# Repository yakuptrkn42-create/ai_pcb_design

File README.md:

# AİES — kalp anatomi eğitim cihazı

**Güncel teslim:** videodan gözlem kaydı ve ayrı bir bağlantı önerisi; paylaşılan üç blok görseli KiCad sayfaları olarak da oluşturuldu.

- [Tüm KiCad projeleri, PDF, parça/GPIO tabloları ve video kanıtları — ZIP](AIES_Kalp_Anatomi_KiCad_Rev1.zip)
- [Bağlantı önerisi P1 — 7 sayfalı PDF](AIES_Video_Schematic_Review_R1/PDF/AIES_Oneri_P1.pdf)
- [Video inceleme raporu ve yakın görüntüler — PDF](AIES_Video_Schematic_Review_R1/PDF/Inceleme_Raporu_TR.pdf)
- [Açılış ve kapsam](AIES_Video_Schematic_Review_R1/README_TR.md) · [Zaman/kesinlik tablosu](AIES_Video_Schematic_Review_R1/Review/Inceleme_Tablosu.csv)

Öneri projesini `AIES_Video_Schematic_Review_R1/Proposal/Project/AIES_Oneri_P1.kicad_pro` ile KiCad 9'da açın. **P1 ERC: 0 hata / 0 uyarı; 157 pin–net eşlemesi kontrol edildi.** GPIO/adres/LED sırası mühendislik seçimidir; mevcut yüklü firmware uyumu bilinmiyor, uyarlama gerektirir.

`Project/` altındaki video kaydı ayrı tutuldu: bilinmeyen kablolar/GPIO tahmin edilmedi; 68 açık terminal + 8 besleme-sürücü ERC bulgusu saklanmadı. Küçük video 148,89 saniye / 480×848; 3 × 8 görünür LED gövdesi sayıldı. Ses konuşması incelenemedi. Exact modül, güç/USB ve üretici limitleri açık; PCB/firmware veya fiziksel test yapılmadı. Üretime hazır onayı verilmedi.

---

# Güncel teslim — Rev J / Routing R2

**Güncel yüklenen Project.zip temel alınarak routing tamamlandı. 0 DRC ihlali / 0 açık bağlantı / 0 şematik–PCB farkı / ERC 0 hata ve 0 uyarı.**

- [Doğrudan indir — KiCad + Gerber/drill + rapor ZIP](https://github.com/yakuptrkn42-create/ai_pcb_design/raw/refs/heads/main/STM32F469_DISEN_RevJ_Routing_R2.zip)
- [Yalnız üreticiye aktarım dosyaları — CAM ZIP](https://github.com/yakuptrkn42-create/ai_pcb_design/raw/refs/heads/main/STM32F469_DISEN_RevJ_Routing_R2_Fabrication.zip)
- [Beş sayfalık teknik rapor — PDF](SingleLCD_RevJ_Routing_R2/PDF/Routing_R2_Review_TR.pdf)
- [Düzenlenebilir KiCad projesi](SingleLCD_RevJ_Routing_R2/Project/) · [Açılış ve kapsam](SingleLCD_RevJ_Routing_R2/README_TR.md)
- [Gerber/drill doğrulaması](SingleLCD_RevJ_Routing_R2/Verification/Manufacturing_Audit.json) · [Bağımsız elektriksel/routing denetimi](SingleLCD_RevJ_Routing_R2/Verification/Validation_Summary.json)

55 × 45 mm / dört katman; J1/J2/J3 ve dört montaj deliği aynı konumda. DSI iletkenleri ~32,824 mm, her birinde iki via; çift içi planar fark <0,001 mm. İki iç GND düzlemi, backlight güç/Kelvin yolları ve eksik kontrol/besleme bağlantıları tamamlandı. SW dal toplamı 5,54 mm / 0,6 mm; 5 V ana yolları 0,8 mm. R13 8,2k/%1; J6 polarite yazısı düzeltildi. Kaynak 159 pin–net üyeliği korunur.

**Üretim kabulü koşullu:** 100 Ω hedefi için 99,4 Ω maskesiz 2D tahmin nominal kesite aittir; gerçek üretici kesiti/bitmiş geometri ve empedans kabulü henüz doğrulanmadı. FPC/kasa, parça rating'leri, touch gerilim toleransı ve yük/OVP/SI testleri raporda açıktır. Gerber/drill hazırlanmış olması fiziksel çalışma garantisi değildir. CAM ZIP içindeki aktarım koşulları imalat öncesi uygulanmalıdır.

ZIP'i tamamen çıkarıp `SingleLCD_RevJ_Routing_R2/Project/STM32F469_DISEN_RevJ_Prep1.kicad_pro` dosyasını KiCad 9 ile açın. Aşağıdaki teslimler tarihsel olarak korunur; güncel R2 projesiyle karıştırılmamalıdır.

---

# Korunan PCB yerleşimi — J-SR1 / Placement P3

**Placement tamamlandı; routing yapılmadı.** Son J-SR1 şematiği korunarak 55 × 45 mm / dört katmanlı kart yeniden yerleştirildi. J1 sol, J2/J3 üst kenara alındı; DSI için açık L koridoru ve sağ altta kompakt TPS61165 bloğu oluşturuldu. Dört montaj deliği aynı konumda kaldı.

- [Doğrudan indir — P3 KiCad ZIP](https://github.com/yakuptrkn42-create/ai_pcb_design/raw/refs/heads/main/STM32F469_DISEN_RevJ_Placement_P3.zip)
- [Yerleşim incelemesi — dört sayfalık PDF](SingleLCD_RevJ_Placement_P3/PDF/Placement_P3_Review_TR.pdf)
- [Düzenlenebilir KiCad projesi](SingleLCD_RevJ_Placement_P3/Project/) · [Açılış ve kapsam](SingleLCD_RevJ_Placement_P3/README_TR.md)
- [Routing alanı ve via adayları](SingleLCD_RevJ_Placement_P3/Views/Routing_Plan.png) · [Routing devir notları](SingleLCD_RevJ_Placement_P3/Engineering/ROUTING_HANDOFF_TR.md)
- [Doğrulama özeti](SingleLCD_RevJ_Placement_P3/Verification/Validation_Summary.json) · [Taşınabilir proje kontrolü](SingleLCD_RevJ_Placement_P3/Verification/Portable_Check.json)

**0 fiziksel DRC ihlali / 0 parity farkı / ERC 0 hata ve 0 uyarı.** Kartta 0 iz, 0 via ve 0 bakır dolgu var; montaj donanımı için dört keepout/rule area var. Routing yapılmadığı için 115 bağlantısız öğe kaydı beklenir. Üç şematik dosyası byte düzeyinde değişmedi; komponent değerleri, footprint kimlikleri ve pin bağlantıları J-SR1 ile eşleşir.

100 Ω ve iz/skew/via bütçeleri tasarım hedefleridir; üretici stackup'ı ve gerçek routing ile doğrulanmalıdır. İç GND katmanları henüz boş. FPC modelleri nominal; J6 gövdesinin 3D modeli yok. Exact kablo/kasa uyumu fiziksel teyit gerektirir. Bu paket üretim çıktısı değildir; aşağıdaki eski routing teslimleri P3'e uygulanmaz.

ZIP'i tamamen çıkarıp `SingleLCD_RevJ_Placement_P3/Project/STM32F469_DISEN_RevJ_Prep1.kicad_pro` dosyasını KiCad 9 ile açın.

---

# Yeni şematik inceleme — J-SR1

- [KiCad proje paketini indir — ZIP](STM32F469_DISEN_J_SR1_Schematic_Review.zip?raw=true)
- [Revize şematik — PDF](Schematic_RevJ_SR1_Review/PDF/Schematic_J_SR1.pdf)
- [Beş sayfalık teknik rapor — PDF](Schematic_RevJ_SR1_Review/PDF/Engineering_Review_TR.pdf)
- [Native KiCad projesi ve açılış notları](Schematic_RevJ_SR1_Review/README_TR.md)

22 Ekim 2026 tarihinde yüklenen proje üzerinde elektriksel şematik incelemesi: **ERC 0 hata / 0 uyarı**. J6 polarite açıklaması ve J4 konnektör/footprint tanımı düzeltildi; R13 8,2 kΩ yapıldı. 39 LCD pini, 25 host CN10 pini ve 53 footprint'in pin üyeliği doğrulandı. Kaynak ZIP değiştirilmeden paketlendi.

**Koşullu teslim:** host 3,365 V toleransı / touch 3,3 V üst sınırı için DISEN teyidi; gerçek FPC sürekliliği ve OVP açık-yük testleri bekleniyor. Donanımda çalışma ve nihai PCB dondurma onayı verilmedi. Bu revizyon şematik içindir; aşağıdaki önceki routing teslimi güncellenmedi.

---

# DISEN LCD — Rev J / Routing R1

**Güncel teslim: dört katman routing tamamlandı. 0 DRC ihlali / 0 bağlantısız öğe / 0 şematik–PCB parity farkı.**

- [Tek ZIP — KiCad proje, 2D/3D, rapor, Gerber ve drill](STM32F469_DISEN_RevJ_Routing_R1.zip)
- [Kısa mühendislik raporu ve PCB görselleri — PDF](SingleLCD_RevJ_Routing_R1/PDF/Routing_R1_Review_TR.pdf)
- [Native KiCad projesi](SingleLCD_RevJ_Routing_R1/Project/) · [Açılış ve doğrulama notları](SingleLCD_RevJ_Routing_R1/README_TR.md)
- [Final DRC](SingleLCD_RevJ_Routing_R1/Verification/DRC_Final.txt) · [Stackup / kurallar](SingleLCD_RevJ_Routing_R1/Engineering/Stackup_And_Rules_TR.md) · [CAM doğrulaması](SingleLCD_RevJ_Routing_R1/Verification/Manufacturing_Audit.json)

55 × 45 mm, nominal 1,6 mm / dört katman. J1/J2 ana konnektörleri aynı konum/yönde; şematik netler ve değerler korundu. 5 V yolları 0,8 mm; DSI iletkenleri iki via ile ~32,824 mm, çift içi fiziksel fark <0,01 mm. 49 devre referansı / 44 net / 159 pad–net üyeliği. ERC 0 hata / 3 mevcut etiket uyarısı. Yerleşim değişiklikleri raporda ve CSV/JSON dosyalarında açıklandı.

**Üretici henüz seçilmedi:** stackup/100 Ω hedefi nominaldir; üretici empedans teyidi ve rapordaki FPC/parça/OVP koşulları kapanmalıdır. Gerber/drill son mühendislik incelemesi içindir; fiziksel çalışma garantisi verilmez. Orijinal yüklenen ZIP korundu; önceki projeler ayrı duruyor.

ZIP'i tamamen çıkarıp `SingleLCD_RevJ_Routing_R1/Project/STM32F469_DISEN_RevJ_Prep1.kicad_pro` dosyasını KiCad 9 ile açın. GitHub ZIP sayfasındaki **Download raw file** düğmesiyle indirebilirsiniz.

---

# Korunan önceki placement — Rev J P2

**Önceki LCD teslimi:** yeni yüklenen Project.zip üzerinde son şematik kontrolü ve dört katmanlı placement optimizasyonu.

- [Tek ZIP — tüm proje dosyaları](STM32F469_DISEN_RevJ_Placement_P2.zip)
- [Kısa değerlendirme ve PCB görselleri — PDF](SingleLCD_RevJ_Placement_P2/PDF/Placement_P2_Review_TR.pdf)
- [Güncel şematik — PDF](SingleLCD_RevJ_Placement_P2/PDF/STM32F469_DISEN_RevJ_Placement_P2.pdf)
- [Native KiCad projesi](SingleLCD_RevJ_Placement_P2/Project/) · [Açılış notları](SingleLCD_RevJ_Placement_P2/README_TR.md)

55 × 45 mm, nominal 1,6 mm / dört katman; 49 devre referansı ve kullanıcının dört Ø3,5 mm montaj deliği. J6'nın yanlış polarite açıklaması **1=+5V / 2=GND** olarak düzeltildi; J4 üç kablolu PWM/reset/GND arayüzü doğru adlandırıldı. Elektriksel netler değişmedi: 44 net / 159 pin–net üyeliği aynı. Dokuz kart dışı test noktası içeri alındı; üç konnektör yaklaşımı karşılaştırıldı, ortak DSI kenarı ve kısa boost döngüleri seçildi.

**0 iz / 0 via / 0 zone.** ERC 0 hata / 3 mevcut uyarı; fiziksel DRC 0; şema–PCB parity 0. Routing yapılmadığından 115 bağlantısız öğe kaydı açık. Stackup/empedans ve FPC exact mekanik teyitleri raporda açık; üretim kabulü verilmedi. Routing ayrı onay bekler.

ZIP'i tamamen çıkarın ve `SingleLCD_RevJ_Placement_P2/Project/STM32F469_DISEN_RevJ_Prep1.kicad_pro` dosyasını KiCad 9 ile açın. Kaynak basename korunmuş, başlıklar Placement P2 yapılmıştır. GitHub ZIP sayfasındaki **Download raw file** düğmesini kullanabilirsiniz.

---

## Entegre 2S batarya paketi — Rev A

İnfüzyon pompası için iki adet 18650 hücre, BMS ve sabit dört kontaklı dock bağlantısını birleştiren **tasarımcıya aktarım ön tasarımı**.

- [Tüm proje paketi — ZIP](Integrated_Battery_Pack_RevA.zip)
- [Görsel tasarım raporu — PDF](Integrated_Battery_Pack_RevA/Tasarimciya_Aktarim_TR.pdf)
- [KiCad proje dosyaları](Integrated_Battery_Pack_RevA/Project/)
- [STEP / WRL / FreeCAD montajı](Integrated_Battery_Pack_RevA/Mechanical/)
- [Kapsam ve açılış notları](Integrated_Battery_Pack_RevA/README_TR.md)

Nominal 7,4 V / 3500 mAh; yaklaşık 2 A hedefi; 74 × 42 × 29,12 mm nominal montaj zarfı. Kaynak şematik boş olduğundan bağlantılar PCB'den geri kazanıldı. ERC, fiziksel DRC, açık bağlantı ve şema–PCB eşleşme kontrolleri temizdir; IC işlevleri ve BMS ayarları henüz doğrulanmamıştır. **Üretim veya klinik kullanım onayı yoktur.** Kesin hücre, NTC/host uyumu ve fiziksel numune testleri tasarımcı tarafından tamamlanmalıdır.

---

# STM32F469I-DISCO / DISEN — Rev J komponent yerleşimi

**Korunan önceki teslim: DS070HSD39T-132 için Placement P1.** Onaylı tek LCD şematiği korunarak 49 devre footprint’i yerleştirildi. Çift LCD Rev K ayrı korunuyor.

- [Yerleşim teslimatı — ZIP](STM32F469_DISEN_RevJ_Placement_P1.zip)
- [Yerleşim incelemesi — PDF](SingleLCD_RevJ_Placement_P1/PDF/Placement_Review_TR.pdf)
- [Native KiCad projesi](SingleLCD_RevJ_Placement_P1/Project/)
- [Açılış ve kapsam](SingleLCD_RevJ_Placement_P1/README_TR.md)

50 × 42 mm, R2 köşe, nominal 1,6 mm / 4 katman, üst yüz montajı; dört Ø2,7 mm bağlantısız M2.5 montaj deliği. Üç yerleşim yaklaşımı karşılaştırıldı, routing/SI düzeni seçildi ve yeniden iyileştirildi. Şematik, değerler, 57 net / 172 pin–net üyeliği ve mevcut kurallar korundu.

**0 iz / 0 via / 0 zone.** Yerleşim DRC’si 0 fiziksel ihlal, şema–PCB parity 0 fark; routing yapılmadığından 115 bağlantısız öğe kaydı açıktır. ERC 0 hata / 3 mevcut uyarı. Routing, yerleşim onayını bekler. FPC modelleri nominal; exact kontak/latch/kablo ve üretici stackup/empedans teyitleri raporda açıktır.

ZIP’i tamamen çıkarıp `SingleLCD_RevJ_Placement_P1/Project/STM32F469_DISEN_RevJ_Prep1.kicad_pro` dosyasını KiCad 9 ile açın. Onaylı şematiği byte düzeyinde korumak için kaynak basename korunmuştur. GitHub ZIP sayfasında **Download raw file** kullanılabilir.

## Korunan tek LCD PCB hazırlığı

**Güncel çalışma: DS070HSD39T-132 için Rev J / PCB Hazırlık 1.** Yüklenen eski Rev J esas alındı; çift LCD Rev K ayrı korunuyor.

- [Tek LCD hazırlık teslimatı — ZIP](STM32F469_DISEN_RevJ_PCBPrep1.zip)
- [KiCad proje ve kütüphaneleri](SingleLCD_RevJ_PCBPrep/Project/)
- [Doğrulama raporu — PDF](SingleLCD_RevJ_PCBPrep/PDF/Validation_RevJ_Prep1_TR.pdf)
- [Şematik — PDF](SingleLCD_RevJ_PCBPrep/PDF/STM32F469_DISEN_RevJ_Prep1.pdf)
- [Açılış ve kapsam](SingleLCD_RevJ_PCBPrep/README_TR.md)

49 footprint, 57 net ve 49 model bağı; 172 pin/net kontrolü; şema–PCB parity **0 fark**, ERC **0 hata / 3 açıklanmış uyarı**. Elektriksel bağlantılar ve değerler Rev J ile aynıdır. 4 katmanlı nominal stackup ve routing kuralları kaydedildi.

**Yerleşim henüz yapılmadı:** komponentler başlangıç aktarımı olarak (0,0)'da üst üste durur. Kart sınırı, iz, via ve dolgu yoktur. Bu aşamanın DRC çakışmaları gizlenmeden paketlendi; üretim kabulü verilmedi. FPC ve endüktör modelleri nominaldir; exact mekanik/panel/OVP ve üretici stackup koşulları raporda açıktır. Model kontrol panosu görüntüleri adaptör yerleşimi değildir.

ZIP'i tamamen çıkarıp `SingleLCD_RevJ_PCBPrep/Project/STM32F469_DISEN_RevJ_Prep1.kicad_pro` dosyasını KiCad 9 ile açın. GitHub ZIP sayfasındaki **Download raw file** düğmesiyle indirebilirsiniz.

# Korunan çift LCD çalışması — Rev K

**Güncel teslim: ortak 39 pinli donanım ve seçilebilir backlight OVP şematiği.** LCD-A: DS070HSD39T-132; LCD-B: DS0700BOE1A39CO-0180A.

- [Tüm Rev K dosyaları — ZIP](STM32F469_DISEN_RevK_DualLCD_Review.zip)
- [Gerçek şematik, 4 sayfa — PDF](Schematic_RevK_DualLCD/PDF/STM32F469_DISEN_RevK_DualLCD.pdf)
- [Türkçe mühendislik incelemesi — PDF](Schematic_RevK_DualLCD/PDF/Dual_LCD_Engineering_Review_TR.pdf)
- [Açılış, karşılaştırma ve montaj tablosu](Schematic_RevK_DualLCD/README_TR.md)
- [Native KiCad projesi](Schematic_RevK_DualLCD/Project/) · [BOM](Schematic_RevK_DualLCD/BOM/BOM_RevK_FACTORY_HOLD.csv) · [ERC](Schematic_RevK_DualLCD/Verification/ERC_RevK.txt)

**Yeni LCD için yalnızca mekanik çizim mevcut; tam elektriksel uyumluluk onayı verilmedi.** VCI/VDD gerilim aralıkları ve maksimum LED değerleri eksiktir. Varsayılan R4/R23 DNP montajı bir onay bekletme durumudur; tam izolasyon değildir. Panel-B, eksik veriler kapanmadan bağlanıp enerjilendirilmemelidir.

R7 her iki panel için 5,23 Ω / nominal 38,24 mA kaldı. JP1 yalnızca OVP eşiğini seçer: A 2–3 HIGH ≈28,69 V; B 1–2 LOW ≈14,94 V (geçici aday). MIPI yollarına anahtar eklenmedi. ERC: **0 hata / 3 açıklanmış uyarı**; kurallar değiştirilmedi. PCB ve yazılım bu aşamada değiştirilmedi. Eski PCB'ler yeni dört footprint ve bağlantılar için ECO gerektirir.

ZIP'i tamamen çıkarıp `Schematic_RevK_DualLCD/Project/STM32F469_DISEN_RevK.kicad_pro` dosyasını KiCad 9 ile açın. GitHub ZIP sayfasındaki **Download raw file** düğmesi dosyayı indirir. Yüklenen Rev J arşivi teslimin Original klasöründe aynen korunmuştur.

## Korunan önceki teslimler

- [Rev J şematik ZIP](STM32F469_DISEN_RevJ_Schematic_Review.zip) · [Rev J incelemesi](Schematic_RevJ_Review/README_TR.md)
- [Rev I routing ZIP](STM32F469_RevI_Routed_Review.zip) · [Routing incelemesi](PCB_Routing_Review/Routing_Review_TR.pdf)
- [Rev I placement](PCB_Placement_Review/Placement_Review.pdf) · [Placement ZIP](STM32F469_RevI_Placement_Review.zip)
- [Rev I şematik PDF](STM32F469_RevI_Professional.pdf) · [Şematik KiCad arşivi](STM32F469_RevI_Professional_KiCad.zip)

Tarihsel dosyalar değiştirilmedi; Rev K'nin yeni devresini içermezler. Önceki Gerber'ler Rev K üretim çıktısı değildir.

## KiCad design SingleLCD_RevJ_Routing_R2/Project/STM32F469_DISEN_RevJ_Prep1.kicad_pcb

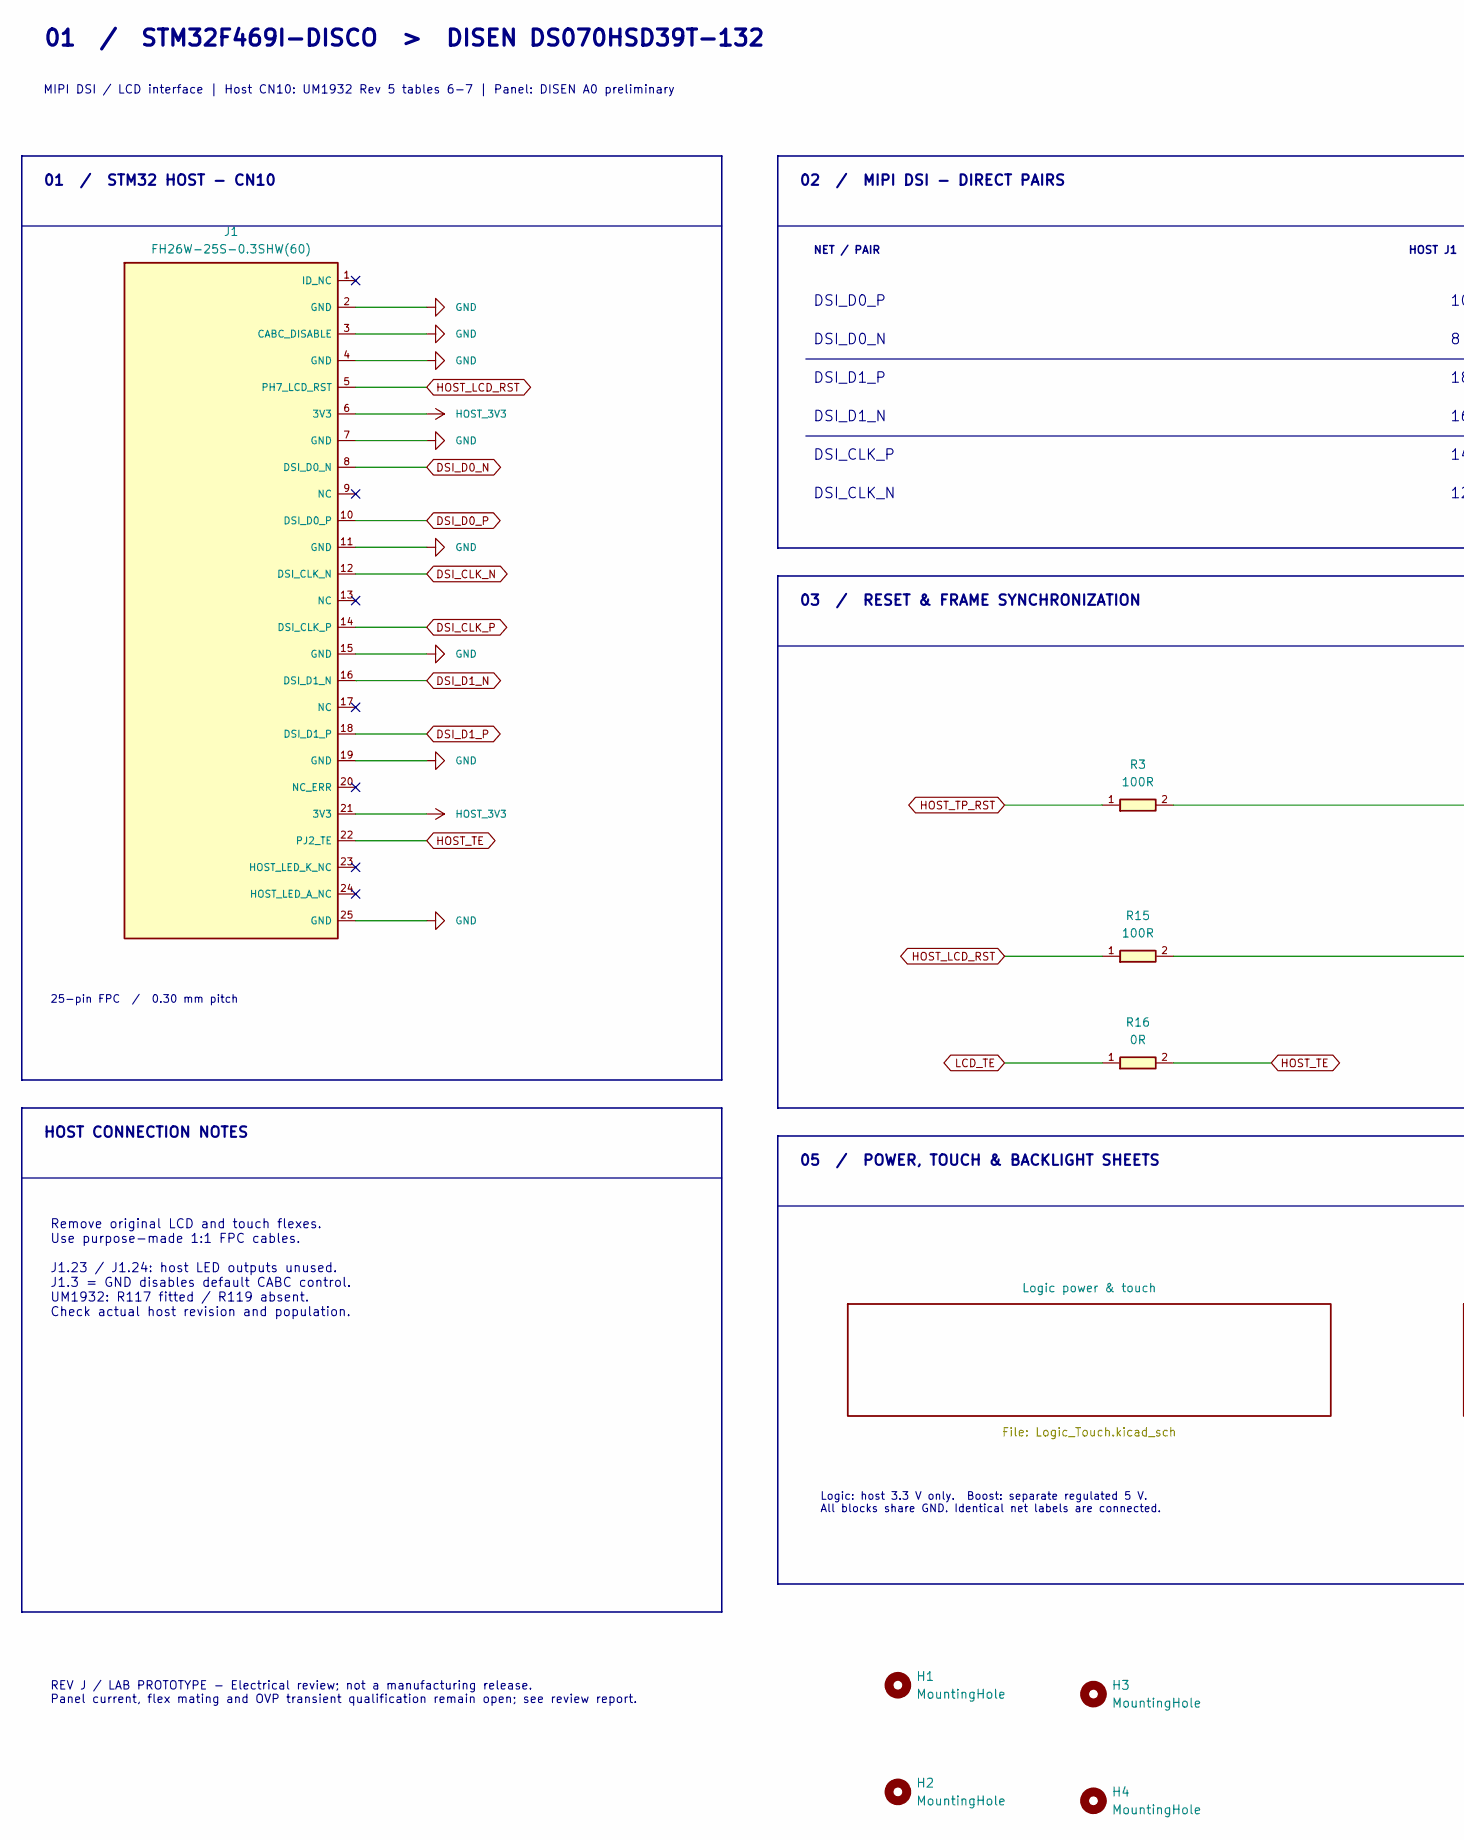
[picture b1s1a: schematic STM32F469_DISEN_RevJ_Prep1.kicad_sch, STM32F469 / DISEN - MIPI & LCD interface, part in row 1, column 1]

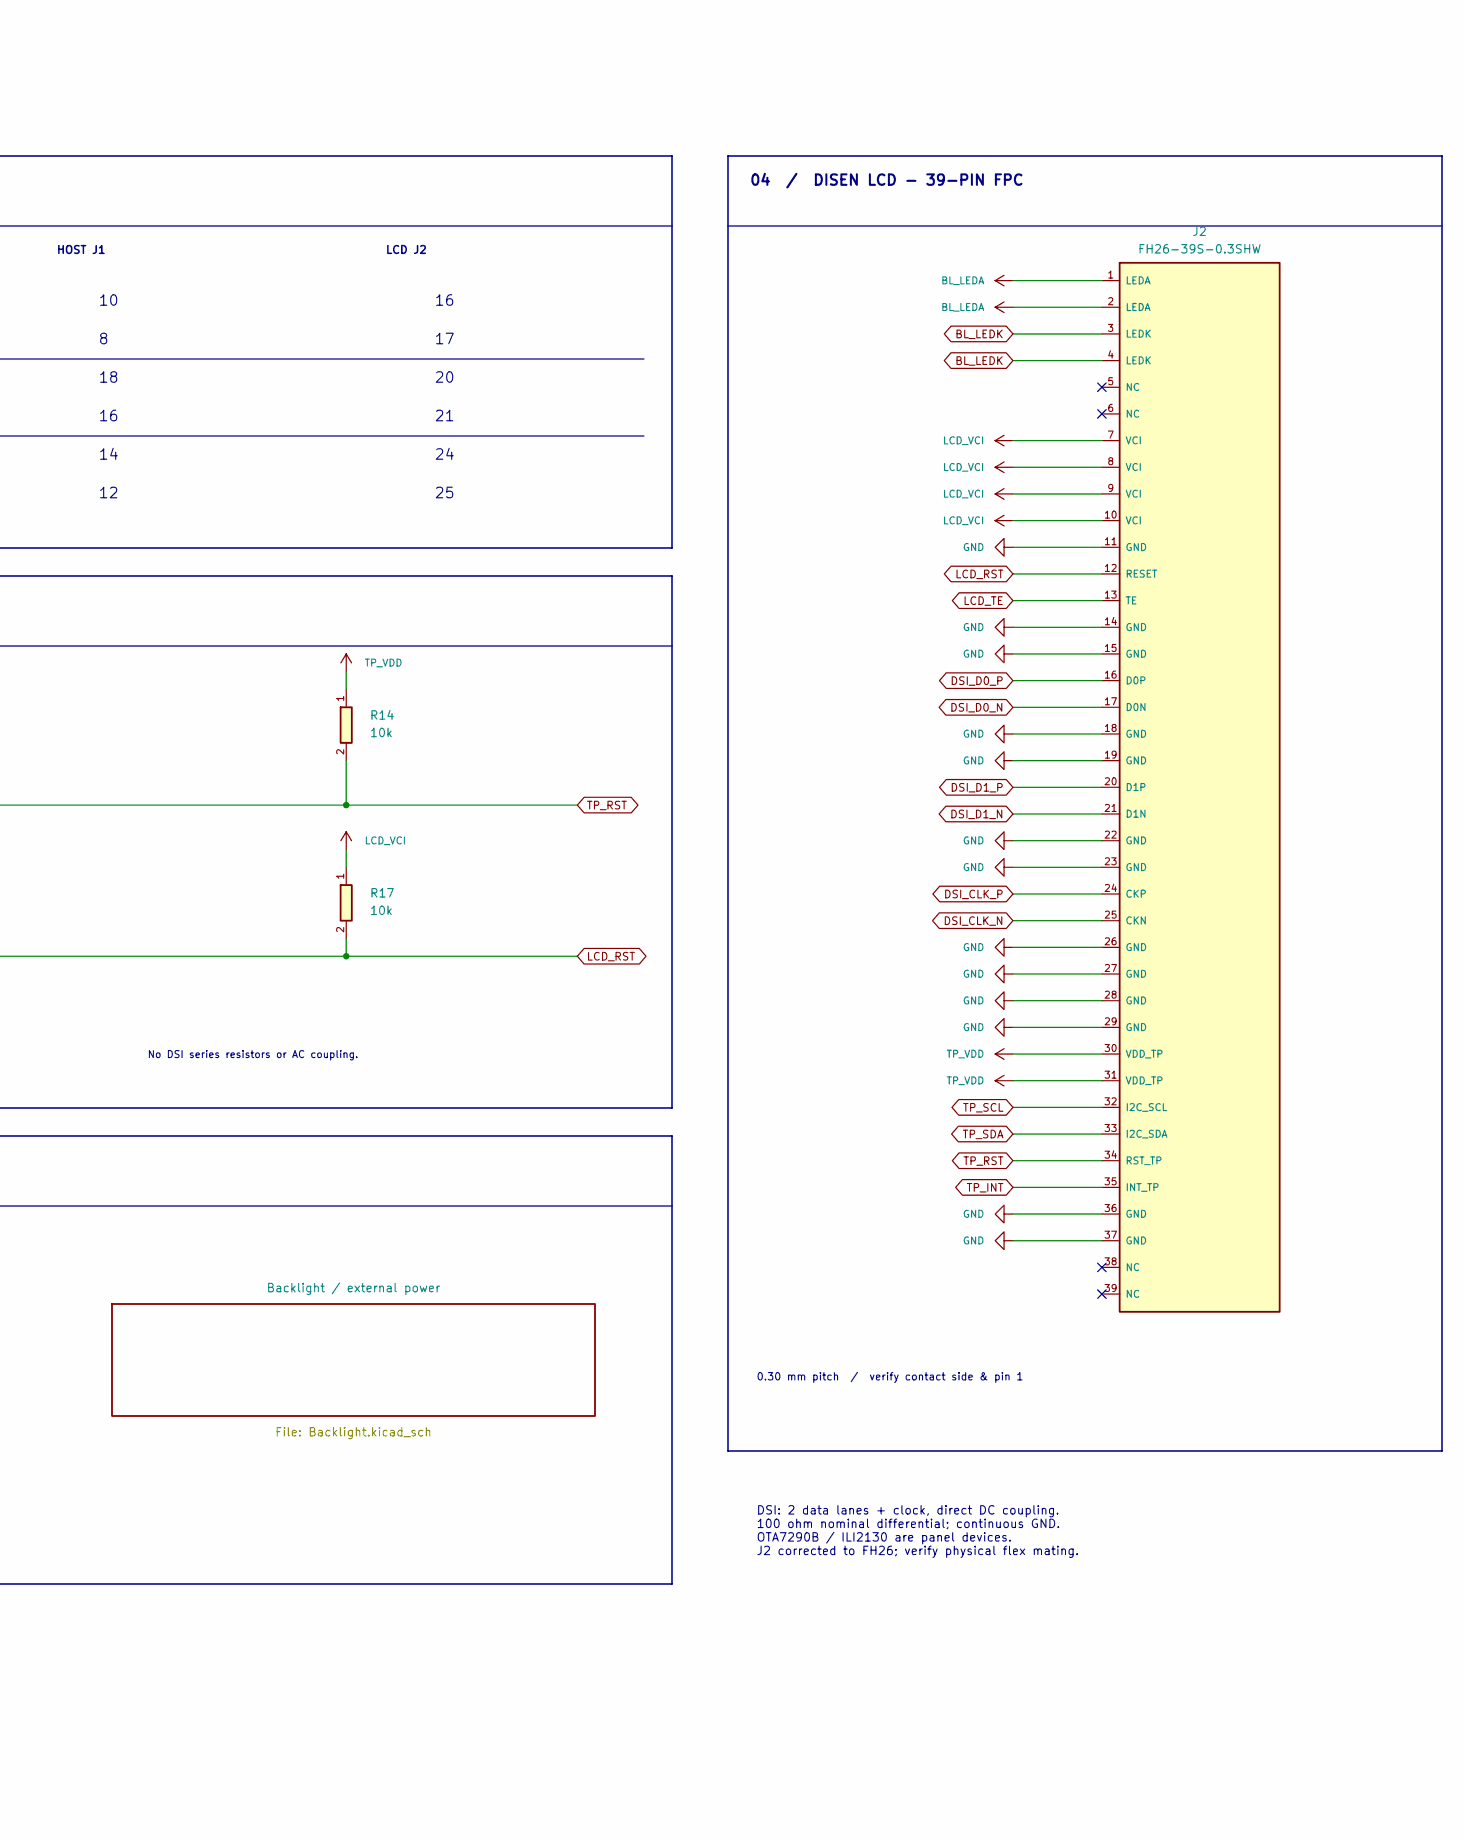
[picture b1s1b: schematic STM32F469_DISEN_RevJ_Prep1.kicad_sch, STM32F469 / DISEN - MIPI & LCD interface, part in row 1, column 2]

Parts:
H1, H2, H3, H4: MountingHole; MountingHole_3.5mm
J1: FH26W-25S-0.3SHW(60); FH26W-25S-0.3SHW; MPN FH26W-25S-0.3SHW(60)
J2: FH26-39S-0.3SHW; MPN FH26-39S-0.3SHW
R3, R15: 100R; R_0805_2012Metric
R14, R17: 10k; R_0805_2012Metric
R16: 0R; R_0805_2012Metric

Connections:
BL_LEDA: J2.1 (LEDA), J2.2 (LEDA); also elsewhere on the board
BL_LEDK: J2.3 (LEDK), J2.4 (LEDK); also elsewhere on the board
DSI_CLK_N: J1.12 (DSI_CLK_N), J2.25 (CKN)
DSI_CLK_P: J1.14 (DSI_CLK_P), J2.24 (CKP)
DSI_D0_N: J1.8 (DSI_D0_N), J2.17 (D0N)
DSI_D0_P: J1.10 (DSI_D0_P), J2.16 (D0P)
DSI_D1_N: J1.16 (DSI_D1_N), J2.21 (D1N)
DSI_D1_P: J1.18 (DSI_D1_P), J2.20 (D1P)
GND: J1.2 (GND), J1.3 (CABC_DISABLE), J1.4 (GND), J1.7 (GND), J1.11 (GND), J1.15 (GND), J1.19 (GND), J1.25 (GND), J2.11 (GND), J2.14 (GND), J2.15 (GND), J2.18 (GND), J2.19 (GND), J2.22 (GND), J2.23 (GND), J2.26 (GND), J2.27 (GND), J2.28 (GND), J2.29 (GND), J2.36 (GND), J2.37 (GND); also elsewhere on the board
HOST_3V3: J1.6 (3V3), J1.21 (3V3); also elsewhere on the board
HOST_LCD_RST: J1.5 (PH7_LCD_RST), R15.1
HOST_TE: J1.22 (PJ2_TE), R16.2
HOST_TP_RST: R3.1; also elsewhere on the board
LCD_RST: J2.12 (RESET), R15.2, R17.2; also elsewhere on the board
LCD_TE: J2.13 (TE), R16.1
LCD_VCI: J2.7 (VCI), J2.8 (VCI), J2.9 (VCI), J2.10 (VCI), R17.1; also elsewhere on the board
TP_INT: J2.35 (INT_TP); also elsewhere on the board
TP_RST: J2.34 (RST_TP), R3.2, R14.2; also elsewhere on the board
TP_SCL: J2.32 (I2C_SCL); also elsewhere on the board
TP_SDA: J2.33 (I2C_SDA); also elsewhere on the board
TP_VDD: J2.30 (VDD_TP), J2.31 (VDD_TP), R14.1; also elsewhere on the board

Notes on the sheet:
MIPI DSI / LCD interface | Host CN10: UM1932 Rev 5 tables 6-7 | Panel: DISEN A0 preliminary
REV J / LAB PROTOTYPE - Electrical review; not a manufacturing release. Panel current, flex mating and OVP transient qualification remain open; see review report.
DSI: 2 data lanes + clock, direct DC coupling. 100 ohm nominal differential; continuous GND. OTA7290B / ILI2130 are panel devices. J2 corrected to FH26; verify physical flex mating.
04 / DISEN LCD - 39-PIN FPC
No DSI series resistors or AC coupling.
0.30 mm pitch / verify contact side & pin 1
01 / STM32 HOST - CN10
DSI_D0_P
DSI_D0_N
25-pin FPC / 0.30 mm pitch
DSI_D1_P
02 / MIPI DSI - DIRECT PAIRS
DSI_D1_N
DSI_CLK_N
Logic: host 3.3 V only. Boost: separate regulated 5 V. All blocks share GND. Identical net labels are connected.
DSI_CLK_P
03 / RESET & FRAME SYNCHRONIZATION
NET / PAIR
01 / STM32F469I-DISCO > DISEN DS070HSD39T-132
LCD J2
HOST CONNECTION NOTES
HOST J1
Remove original LCD and touch flexes. Use purpose-made 1:1 FPC cables. J1.23 / J1.24: host LED outputs unused. J1.3 = GND disables default CABC control. UM1932: R117 fitted / R119 absent. Check actual host revision and population.
05 / POWER, TOUCH & BACKLIGHT SHEETS

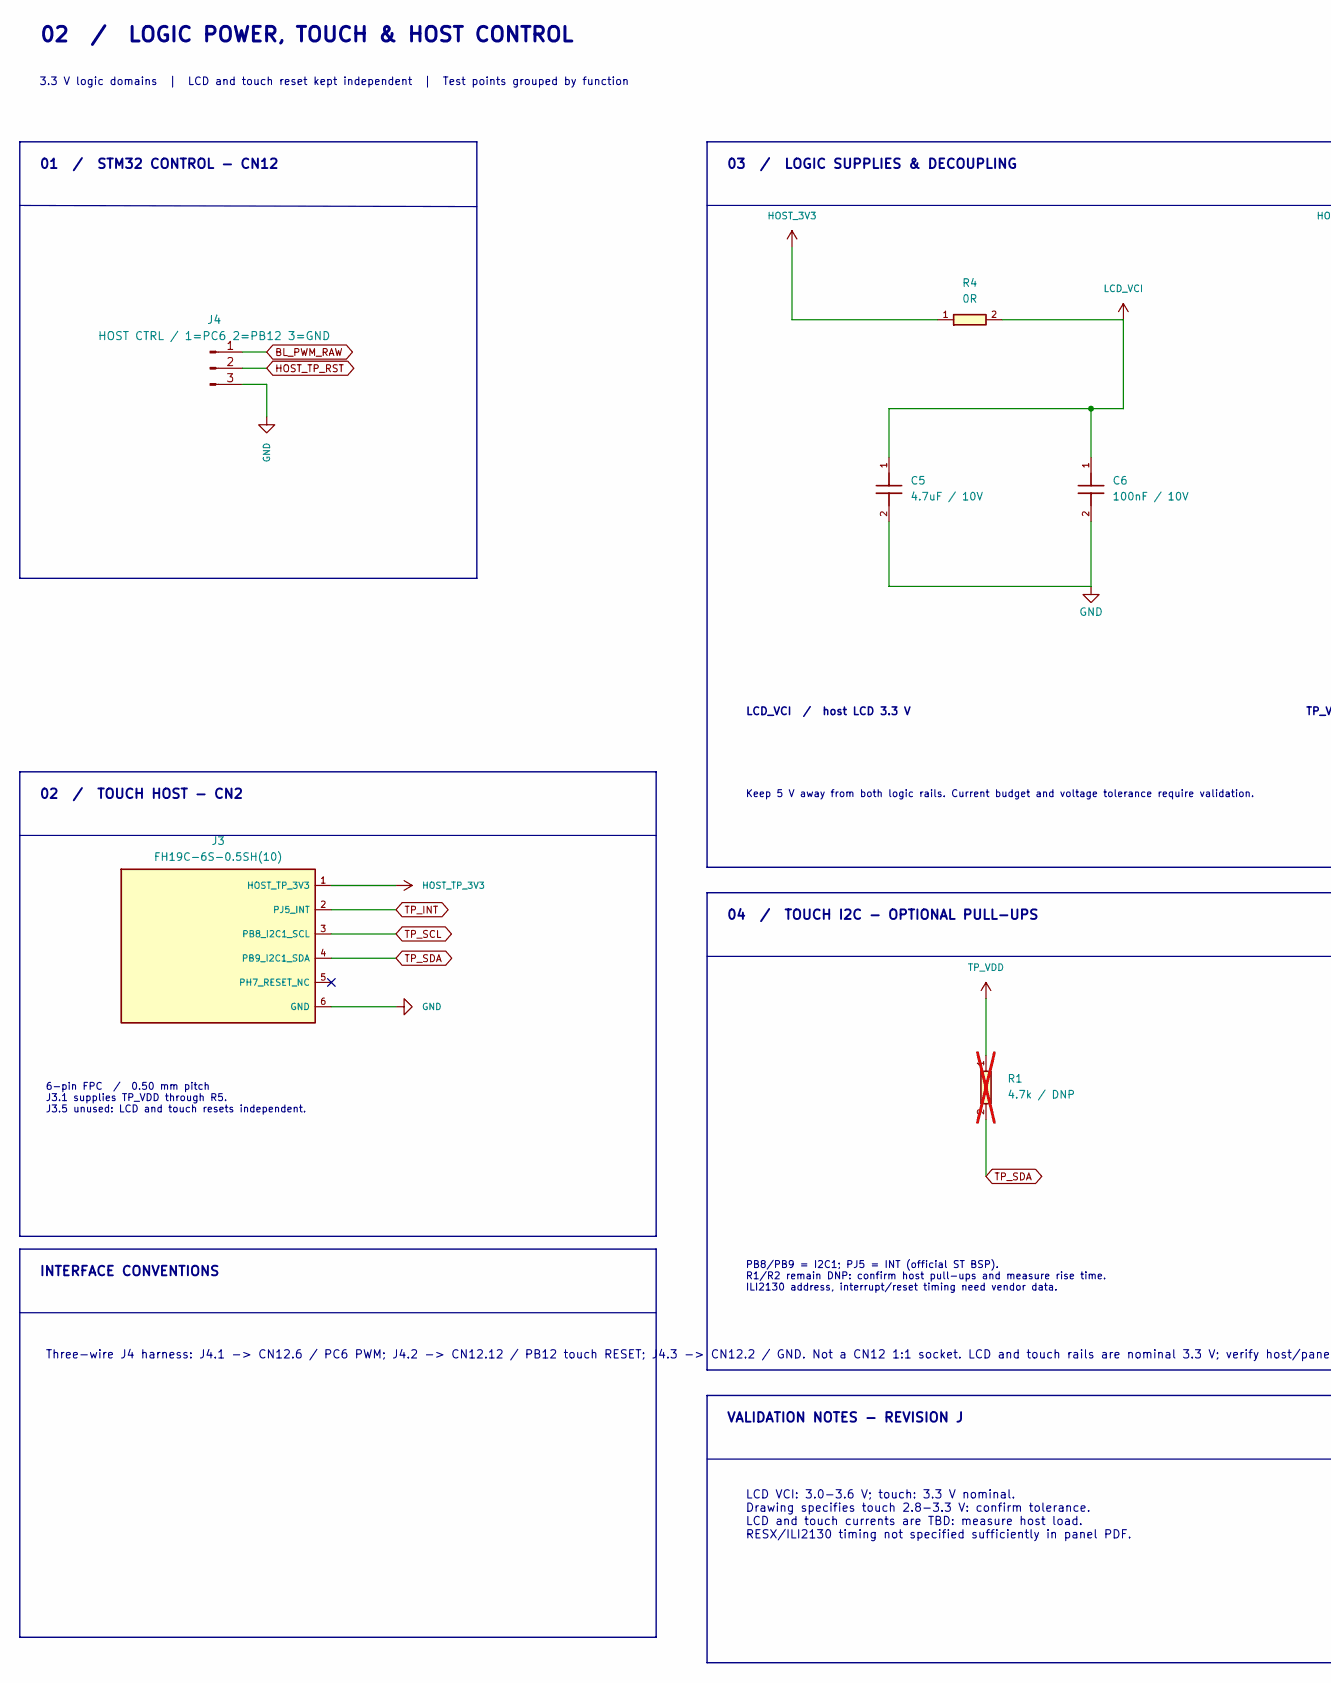
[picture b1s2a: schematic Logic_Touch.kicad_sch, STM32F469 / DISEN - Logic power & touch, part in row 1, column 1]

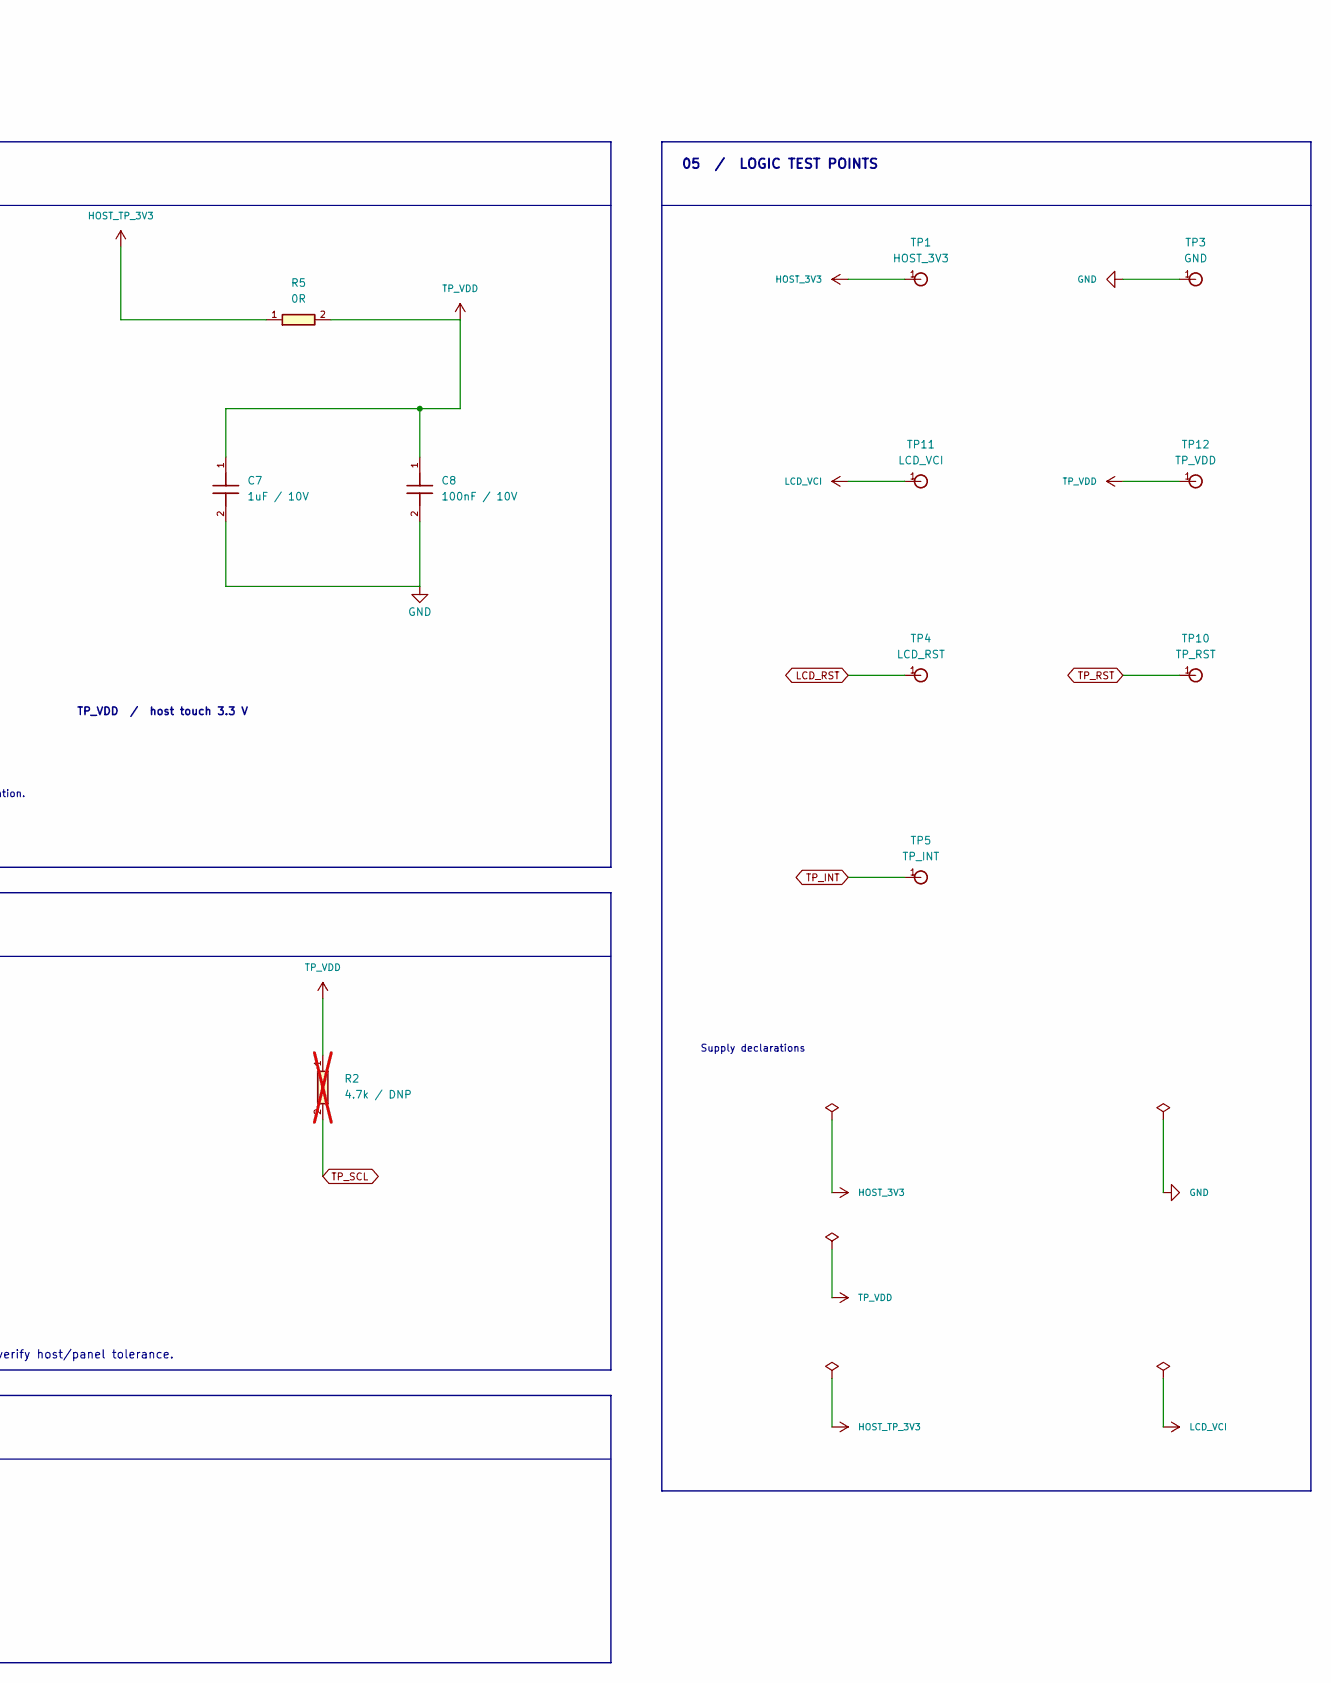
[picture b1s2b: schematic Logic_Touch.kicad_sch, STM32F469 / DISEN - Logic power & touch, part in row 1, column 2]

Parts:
C5: 4.7uF / 10V; C_0805_2012Metric
C6, C8: 100nF / 10V; C_0805_2012Metric
C7: 1uF / 10V; C_0805_2012Metric
J3: FH19C-6S-0.5SH(10); FH19C-6S-0.5SH; MPN FH19C-6S-0.5SH(10)
J4: HOST CTRL / 1=PC6 2=PB12 3=GND; HostCtrl_1x03_Existing
R1, R2: 4.7k / DNP; R_0805_2012Metric; not fitted
R4, R5: 0R; R_0805_2012Metric
TP1: HOST_3V3; TestPoint_Pad_D1.0mm
TP3: GND; TestPoint_Pad_D1.0mm
TP4: LCD_RST; TestPoint_Pad_D1.0mm
TP5: TP_INT; TestPoint_Pad_D1.0mm
TP10: TP_RST; TestPoint_Pad_D1.0mm
TP11: LCD_VCI; TestPoint_Pad_D1.0mm
TP12: TP_VDD; TestPoint_Pad_D1.0mm

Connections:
BL_PWM_RAW: J4.1; also elsewhere on the board
GND: C5.2, C6.2, C7.2, C8.2, J3.6 (GND), J4.3, TP3.1; also elsewhere on the board
HOST_3V3: R4.1, TP1.1; also elsewhere on the board
HOST_TP_3V3: J3.1 (HOST_TP_3V3), R5.1
HOST_TP_RST: J4.2; also elsewhere on the board
LCD_RST: TP4.1; also elsewhere on the board
LCD_VCI: C5.1, C6.1, R4.2, TP11.1; also elsewhere on the board
TP_INT: J3.2 (PJ5_INT), TP5.1; also elsewhere on the board
TP_RST: TP10.1; also elsewhere on the board
TP_SCL: J3.3 (PB8_I2C1_SCL), R2.2; also elsewhere on the board
TP_SDA: J3.4 (PB9_I2C1_SDA), R1.2; also elsewhere on the board
TP_VDD: C7.1, C8.1, R1.1, R2.1, R5.2, TP12.1; also elsewhere on the board

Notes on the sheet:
LCD VCI: 3.0-3.6 V; touch: 3.3 V nominal. Drawing specifies touch 2.8-3.3 V: confirm tolerance. LCD and touch currents are TBD: measure host load. RESX/ILI2130 timing not specified sufficiently in panel PDF.
INTERFACE CONVENTIONS
PB8/PB9 = I2C1; PJ5 = INT (official ST BSP). R1/R2 remain DNP: confirm host pull-ups and measure rise time. ILI2130 address, interrupt/reset timing need vendor data.
TP_VDD / host touch 3.3 V
Three-wire J4 harness: J4.1 -> CN12.6 / PC6 PWM; J4.2 -> CN12.12 / PB12 touch RESET; J4.3 -> CN12.2 / GND. Not a CN12 1:1 socket. LCD and touch rails are nominal 3.3 V; verify host/panel tolerance.
05 / LOGIC TEST POINTS
6-pin FPC / 0.50 mm pitch J3.1 supplies TP_VDD through R5. J3.5 unused: LCD and touch resets independent.
02 / TOUCH HOST - CN2
02 / LOGIC POWER, TOUCH & HOST CONTROL
LCD_VCI / host LCD 3.3 V
04 / TOUCH I2C - OPTIONAL PULL-UPS
01 / STM32 CONTROL - CN12
3.3 V logic domains | LCD and touch reset kept independent | Test points grouped by function
Supply declarations
03 / LOGIC SUPPLIES & DECOUPLING
VALIDATION NOTES - REVISION J
Keep 5 V away from both logic rails. Current budget and voltage tolerance require validation.
